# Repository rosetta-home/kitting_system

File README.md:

# KittingSystem

**TODO: Add description**

## Installation

If [available in Hex](https://hex.pm/docs/publish), the package can be installed
by adding `kitting_system` to your list of dependencies in `mix.exs`:

```elixir
def deps do
  [{:kitting_system, "~> 0.1.0"}]
end
```

Documentation can be generated with [ExDoc](https://github.com/elixir-lang/ex_doc)
and published on [HexDocs](https://hexdocs.pm). Once published, the docs can
be found at [https://hexdocs.pm/kitting_system](https://hexdocs.pm/kitting_system).

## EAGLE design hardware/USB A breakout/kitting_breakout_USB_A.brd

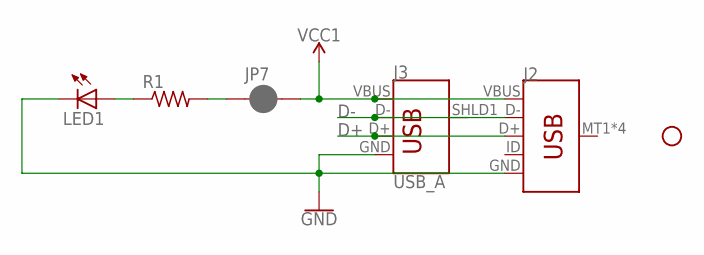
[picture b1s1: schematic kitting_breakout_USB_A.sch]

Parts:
H1: STAND-OFF
J2: USB_MICRO-B_SMT; USB-MICROB
J3: USB_A; USB-A-H-FEMALE-VRT-PTH
JP7: JUMPER-SMT_2_NC_PASTE_SILK; SMT-JUMPER_2_NC_PASTE_SILK
LED1: LEDCHIPLED_0805; CHIPLED_0805
R1: R-US_R0805; R0805

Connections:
D+: J2.D+, J3.D+
D-: J2.D-, J3.D-
GND: J2.GND, J3.GND, LED1.C
unnamed: LED1.A, R1.1
unnamed: JP7.1, R1.2
VCC1: J2.VBUS, J3.VBUS, JP7.2

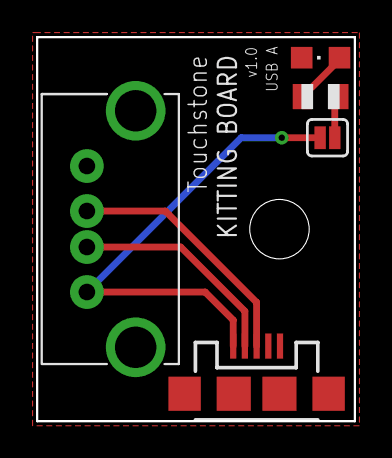
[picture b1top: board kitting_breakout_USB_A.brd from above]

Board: 2 copper layers, 17.7 x 21.3 mm, 6 parts (0 on the bottom side), 6 nets.

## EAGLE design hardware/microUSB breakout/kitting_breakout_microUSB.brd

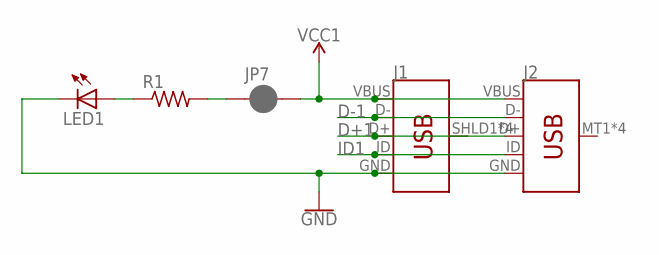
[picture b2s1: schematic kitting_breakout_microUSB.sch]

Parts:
J1: USB_MICRO-B_MALE-VERT; USB_MICROB_VERTICAL
J2: USB_MICRO-B_SMT; USB-MICROB
JP7: JUMPER-SMT_2_NC_PASTE_SILK; SMT-JUMPER_2_NC_PASTE_SILK
LED1: LEDCHIPLED_0805; CHIPLED_0805
R1: R-US_R0805; R0805

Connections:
D+1: J1.D+, J2.D+
D-1: J1.D-, J2.D-
GND: J1.GND, J2.GND, LED1.C
ID1: J1.ID, J2.ID
unnamed: LED1.A, R1.1
unnamed: JP7.1, R1.2
VCC1: J1.VBUS, J2.VBUS, JP7.2

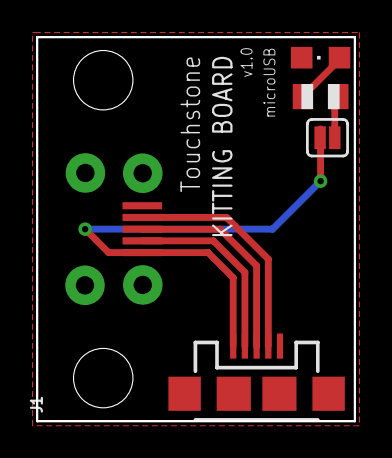
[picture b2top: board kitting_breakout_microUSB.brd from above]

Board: 2 copper layers, 17.7 x 21.3 mm, 5 parts (0 on the bottom side), 7 nets.

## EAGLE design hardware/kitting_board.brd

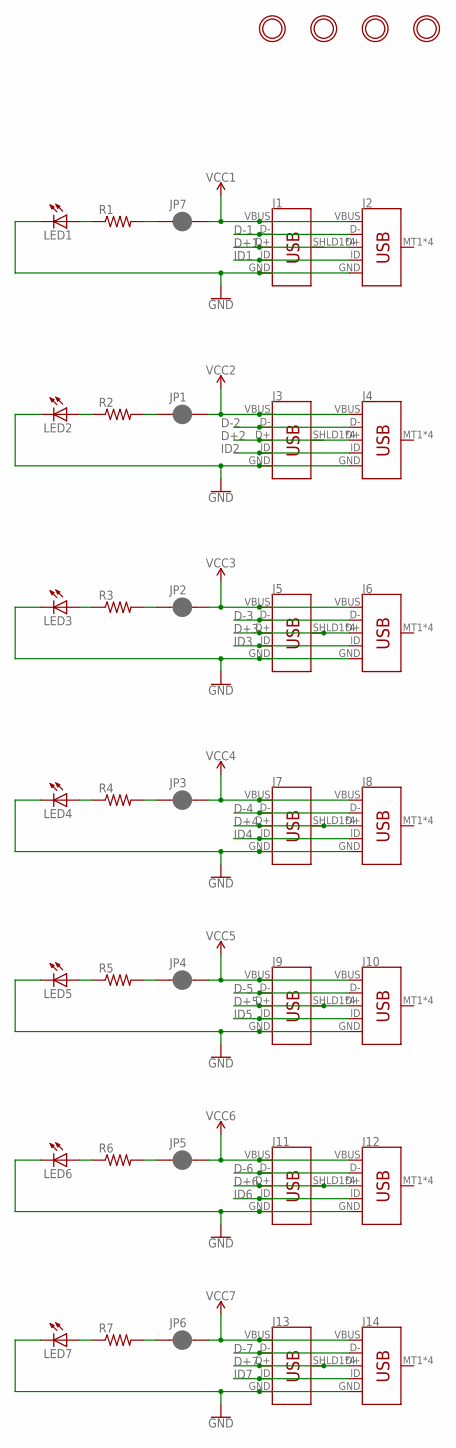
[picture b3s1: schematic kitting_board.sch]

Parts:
J1, J3, J5, J7, J9, J11, J13: USB_MICRO-B_MALE-VERT; USB_MICROB_VERTICAL
J2, J4, J6, J8, J10, J12, J14: USB_MICRO-B_SMT; USB-MICROB
JP1, JP2, JP3, JP4, JP5, JP6, JP7: JUMPER-SMT_2_NC_PASTE_SILK; SMT-JUMPER_2_NC_PASTE_SILK
LED1, LED2, LED3, LED4, LED5, LED6, LED7: LEDCHIPLED_0805; CHIPLED_0805
R1, R2, R3, R4, R5, R6, R7: R-US_R0805; R0805
U$1, U$2, U$3, U$4: MOUNTINGHOLE3.0THIN; MOUNTINGHOLE_3.0_PLATEDTHIN

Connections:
D+1: J1.D+, J2.D+
D+2: J3.D+, J4.D+
D+3: J5.D+, J5.SHLD1 (SHIELD), J5.SHLD2 (SHIELD), J5.SHLD3 (SHIELD), J5.SHLD4 (SHIELD), J6.D+
D+4: J7.D+, J7.SHLD1 (SHIELD), J7.SHLD2 (SHIELD), J7.SHLD3 (SHIELD), J7.SHLD4 (SHIELD), J8.D+
D+5: J9.D+, J9.SHLD1 (SHIELD), J9.SHLD2 (SHIELD), J9.SHLD3 (SHIELD), J9.SHLD4 (SHIELD), J10.D+
D+6: J11.D+, J11.SHLD1 (SHIELD), J11.SHLD2 (SHIELD), J11.SHLD3 (SHIELD), J11.SHLD4 (SHIELD), J12.D+
D+7: J13.D+, J13.SHLD1 (SHIELD), J13.SHLD2 (SHIELD), J13.SHLD3 (SHIELD), J13.SHLD4 (SHIELD), J14.D+
D-1: J1.D-, J2.D-
D-2: J3.D-, J4.D-
D-3: J5.D-, J6.D-
D-4: J7.D-, J8.D-
D-5: J9.D-, J10.D-
D-6: J11.D-, J12.D-
D-7: J13.D-, J14.D-
GND: J1.GND, J2.GND, J3.GND, J4.GND, J5.GND, J6.GND, J7.GND, J8.GND, J9.GND, J10.GND, J11.GND, J12.GND, J13.GND, J14.GND, LED1.C, LED2.C, LED3.C, LED4.C, LED5.C, LED6.C, LED7.C
ID1: J1.ID, J2.ID
ID2: J3.ID, J4.ID
ID3: J5.ID, J6.ID
ID4: J7.ID, J8.ID
ID5: J9.ID, J10.ID
ID6: J11.ID, J12.ID
ID7: J13.ID, J14.ID
unnamed: LED2.A, R2.1
unnamed: JP1.1, R2.2
unnamed: LED3.A, R3.1
unnamed: JP2.1, R3.2
unnamed: LED4.A, R4.1
unnamed: LED1.A, R1.1
unnamed: JP7.1, R1.2
unnamed: JP3.1, R4.2
unnamed: LED5.A, R5.1
unnamed: JP4.1, R5.2
unnamed: LED6.A, R6.1
unnamed: JP5.1, R6.2
unnamed: LED7.A, R7.1
unnamed: JP6.1, R7.2
VCC1: J1.VBUS, J2.VBUS, JP7.2
VCC2: J3.VBUS, J4.VBUS, JP1.2
VCC3: J5.VBUS, J6.VBUS, JP2.2
VCC4: J7.VBUS, J8.VBUS, JP3.2
VCC5: J9.VBUS, J10.VBUS, JP4.2
VCC6: J11.VBUS, J12.VBUS, JP5.2
VCC7: J13.VBUS, J14.VBUS, JP6.2

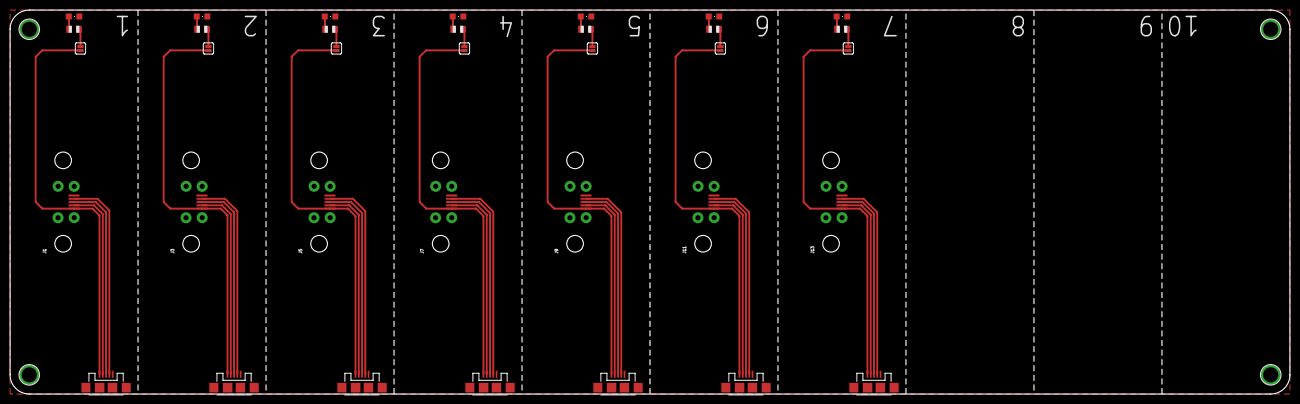
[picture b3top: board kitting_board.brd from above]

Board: 2 copper layers, 254.0 x 76.2 mm, 39 parts (0 on the bottom side), 43 nets.

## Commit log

2017-05-09 initial commit, adds zebra printing support
2017-05-09 do not commit compiled labels
2017-05-10 adds web interface to accept mac address, save to db, print label
2017-05-10 adds config for number of labels to print
2017-05-10 adds skelton for compiling and burning
2017-05-11 adds submodules for compiling systems
2017-05-11 arduino builds working
2017-05-11 adds nerves firmware building
2017-05-11 update new rosetta home
2017-05-11 update compile commands
2017-05-11 remove loop
2017-05-12 make IEQ compile
2017-05-12 adds web-based QR Code Reader
2017-05-22 upgrade rosetta_home to latest
2017-05-22 update return from touchstone compiler
2017-05-30 adds feedback for compiling and burning
2017-05-30 update submodule system directories location
2017-05-30 templatize gateway and touchstone config
2017-06-06 Added kitting board PCB files
    init - design not complete
2017-06-06 Added parts, completed traces
    Added silkscreen
2017-06-07 Added breakout boards for kitting system
    microUSB and USB-A-female
2017-06-07 Added mounting hole on USB A breakout
2017-07-27 adds arduino flashing and cleans up web interface feedback
2018-01-08 add backup and versoined uploads for mongo data
2018-02-08 adding hardware_verification
2018-02-08 update hardware_verification submodule
2018-02-08 adds hardware_verification to kitting system
2018-02-09 concurrent compilation and flashing of touchstones
2018-02-09 update gateway build path, clean up output for compiliation and flashing
2018-02-12 provide feedback to web UI
2018-02-13 update web UI feedback
2018-02-14 update UI and better feedback
2018-02-21 update rosetta_home to latest
2018-02-21 compile and flash nerves hub system
2018-02-22 hub firmware flashing and certificate to application partition
2018-02-22 update rosetta_home commit
2018-02-23 make sure SD card is unmounted

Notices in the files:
parts and their libraries:
SparkFun-Connectors: Licensing: Creative Commons ShareAlike 4.0 International - https://creativecommons.org/licenses/by-sa/4.0
